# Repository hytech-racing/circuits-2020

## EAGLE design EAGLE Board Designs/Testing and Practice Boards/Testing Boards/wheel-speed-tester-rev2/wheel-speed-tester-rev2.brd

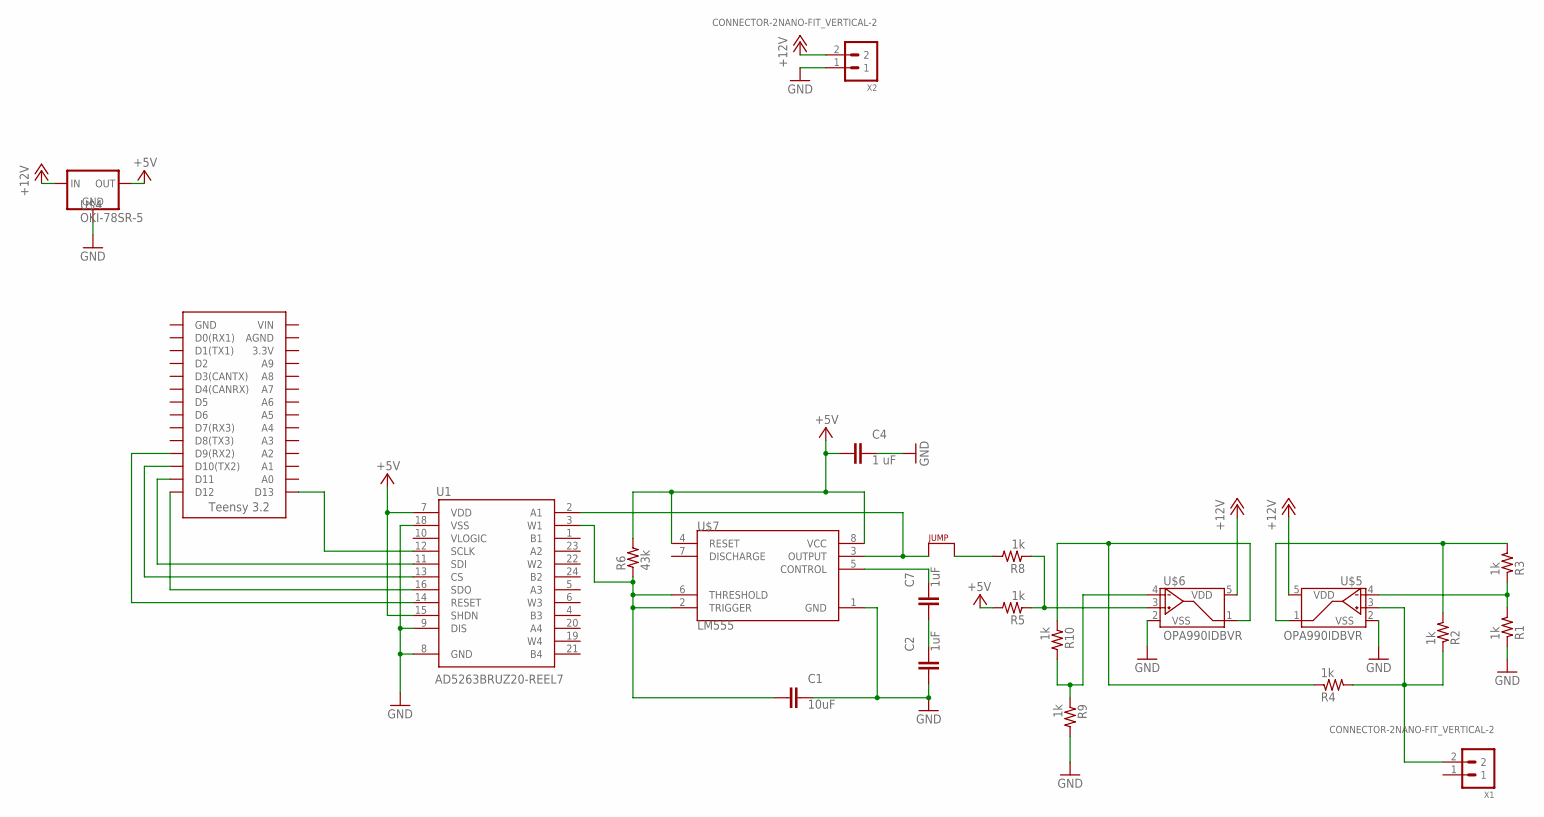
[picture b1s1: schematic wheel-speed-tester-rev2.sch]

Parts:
C1: 10uF; 0603-CAP
C2, C7: 1uF; 0603-CAP
C4: 1 uF; 0603-CAP
J2: JUMPER.1; 1X02
R1, R2, R3, R4, R5, R8, R9, R10: 1k; 0603-RES
R6: 43k; 0603-RES
U1: AD5263BRUZ20-REEL7; TSSOP-24
U$2: TEENSY_3.2_SIMPLE
U$4: OKI-78SR-5; OKI-78SR
U$5, U$6: OPA990IDBVR; SOT-23-5
U$7: LM555; SOIC-08
X1, X2: CONNECTOR-2NANO-FIT_VERTICAL-2; 1053091202

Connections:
+5V: C4.2, R5.2, R6.2, U1.7 (VDD), U1.15 (SHDN), U$4.3 (OUT), U$7.4 (RESET), U$7.8 (VCC)
+12V: U$4.1 (IN), U$5.5 (VDD), U$6.5 (VDD), X2.2
ALTERNATINGVOLTAGE: R4.1, R10.1, U$6.1 (VOUT)
CS: U1.13 (CS), U$2.D10(TX2)
GND: C1.1, C2.2, C4.1, R1.1, R9.2, U1.8 (GND), U1.9 (DIS), U1.18 (VSS), U$4.2 (GND), U$5.2 (VSS), U$6.2 (VSS), U$7.1 (GND), X2.1
unnamed: R2.2, R3.2, U$5.1 (VOUT)
unnamed: R1.2, R3.1, U$5.4 (VIN-)
unnamed: C7.1, U$7.5 (CONTROL)
unnamed: J2.2, R8.2
unnamed: R5.1, R8.1, U$6.3 (VIN+)
unnamed: C2.1, C7.2
unnamed: J2.1, U1.2 (A1), U$7.3 (OUTPUT)
unnamed: R9.1, R10.2, U$6.4 (VIN-)
unnamed: U1.11 (SDI), U$2.D11
unnamed: U1.16 (SDO), U$2.D12
unnamed: C1.2, R6.1, U1.3 (W1), U$7.2 (TRIGGER), U$7.6 (THRESHOLD)
RESET: U1.14 (RESET), U$2.D9(RX2)
SCLK: U1.12 (SCLK), U$2.D13
WSTESTER_OUT: R2.1, R4.2, U$5.3 (VIN+), X1.2

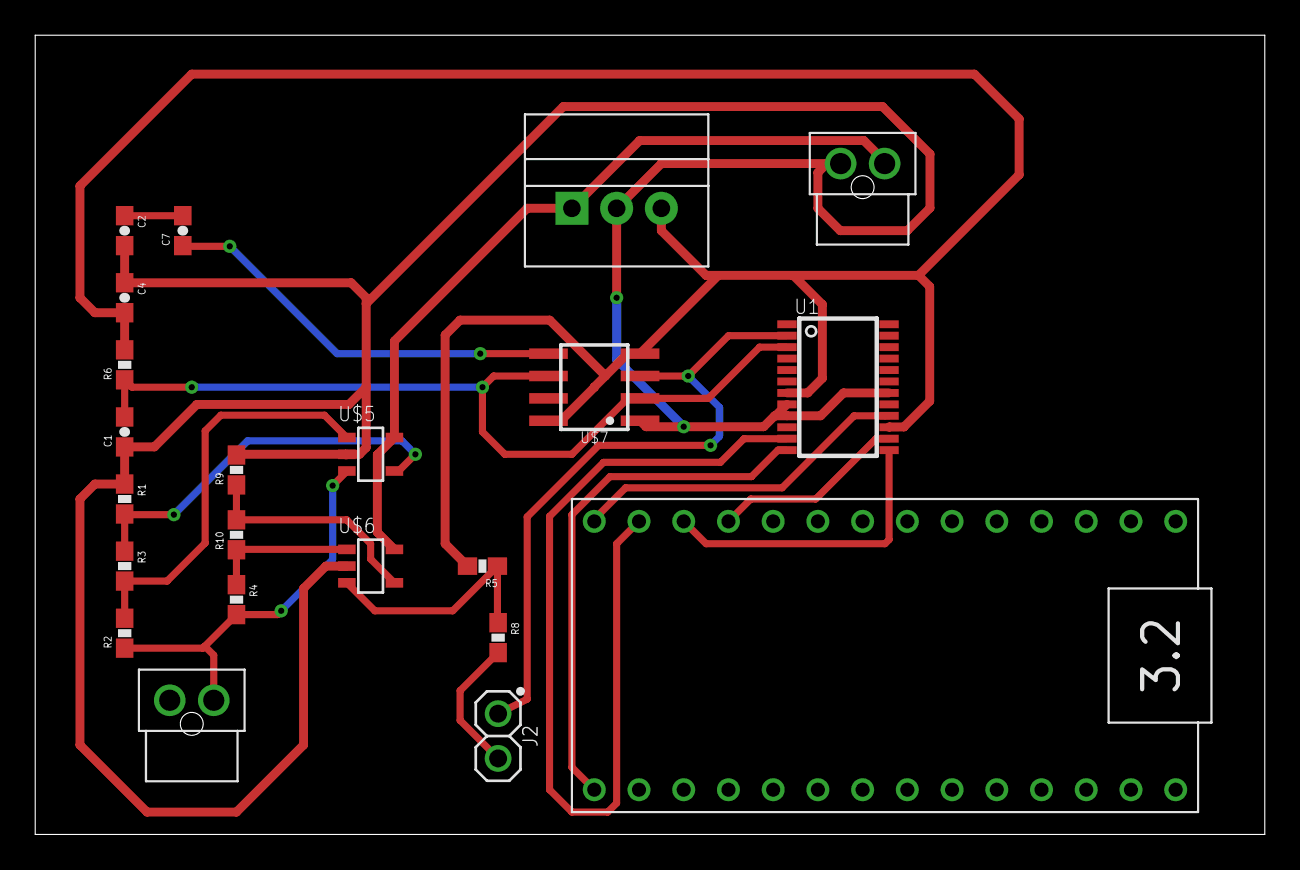
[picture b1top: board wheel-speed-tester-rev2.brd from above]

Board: 2 copper layers, 69.8 x 45.4 mm, 22 parts (0 on the bottom side), 19 nets.

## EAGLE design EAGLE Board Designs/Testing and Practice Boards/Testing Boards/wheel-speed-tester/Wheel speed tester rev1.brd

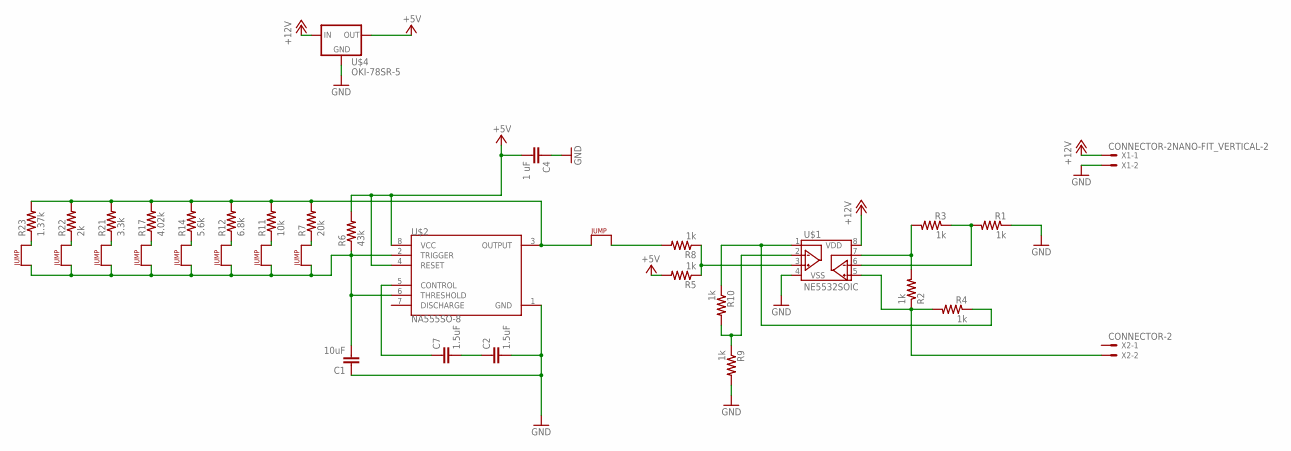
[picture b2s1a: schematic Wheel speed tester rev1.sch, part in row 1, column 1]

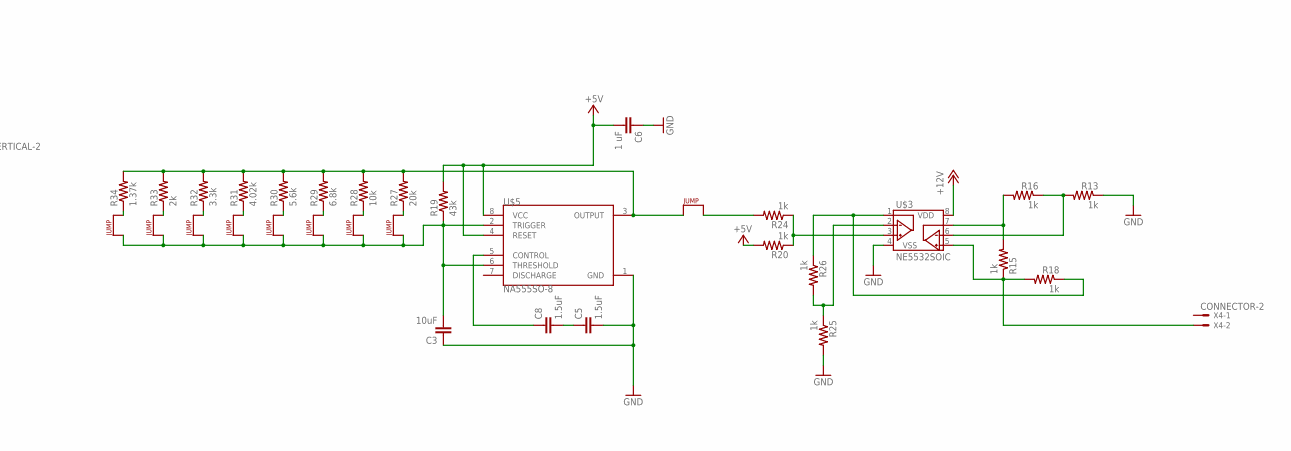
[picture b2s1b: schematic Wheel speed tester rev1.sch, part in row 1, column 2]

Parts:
C1, C3: 10uF; 0603-CAP
C2, C5, C7, C8: 1.5uF; 0603-CAP
C4, C6: 1 uF; 0603-CAP
J1, J2, J3, J4, J5, J6, J7, J8, J9, J10, J11, J12, J13, J14, J15, J16, J17, J18: JUMPER.1; 1X02
R1, R2, R3, R4, R5, R8, R9, R10, R13, R15, R16, R18, R20, R24, R25, R26: 1k; 0603-RES
R6, R19: 43k; 0603-RES
R7, R27: 20k; 0603-RES
R11, R28: 10k; 0603-RES
R12, R29: 6.8k; 0603-RES
R14, R30: 5.6k; 0603-RES
R17, R31: 4.02k; 0603-RES
R21, R32: 3.3k; 0603-RES
R22, R33: 2k; 0603-RES
R23, R34: 1.37k; 0603-RES
U$1, U$3: NE5532SOIC; SOIC-08
U$2, U$5: NA555SO-8; SOIC-08
U$4: OKI-78SR-5; OKI-78SR
X1: CONNECTOR-2NANO-FIT_VERTICAL-2; NANO-FIT_VERTICAL-2
X2, X4: CONNECTOR-2; MINIFIT_5566-2

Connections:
+5V: C4.2, C6.2, R5.2, R6.2, R19.2, R20.2, U$2.4 (RESET), U$2.8 (VCC), U$4.3 (OUT), U$5.4 (RESET), U$5.8 (VCC)
+12V: U$1.8 (VDD), U$3.8 (VDD), U$4.1 (IN), X1.P$1
ALTERNATINGVOLTAGE: R4.1, R10.1, U$1.1 (VOUTA)
ALTERNATINGVOLTAGE1: R18.1, R26.1, U$3.1 (VOUTA)
GND: C1.1, C2.2, C3.1, C4.1, C5.2, C6.1, R1.1, R9.2, R13.1, R25.2, U$1.4 (VSS), U$2.1 (GND), U$3.4 (VSS), U$4.2 (GND), U$5.1 (GND), X1.P$2
unnamed: R2.2, R3.2, U$1.7 (VOUTB)
unnamed: R1.2, R3.1, U$1.6 (VINB-)
unnamed: C7.1, U$2.5 (CONTROL)
unnamed: J2.2, R8.2
unnamed: C1.2, J1.1, J3.1, J4.1, J5.1, J6.1, J7.1, J8.1, J9.1, R6.1, U$2.2 (TRIGGER), U$2.6 (THRESHOLD)
unnamed: R5.1, R8.1, U$1.3 (VINA+)
unnamed: J9.2, R7.1
unnamed: J2.1, R7.2, R11.2, R12.2, R14.2, R17.2, R21.2, R22.2, R23.2, U$2.3 (OUTPUT)
unnamed: R9.1, R10.2, U$1.2 (VINA-)
unnamed: J8.2, R11.1
unnamed: J7.2, R12.1
unnamed: J6.2, R14.1
unnamed: J5.2, R17.1
unnamed: J4.2, R21.1
unnamed: J3.2, R22.1
unnamed: J1.2, R23.1
unnamed: R13.2, R16.1, U$3.6 (VINB-)
unnamed: J10.1, R27.2, R28.2, R29.2, R30.2, R31.2, R32.2, R33.2, R34.2, U$5.3 (OUTPUT)
unnamed: R20.1, R24.1, U$3.3 (VINA+)
unnamed: R15.2, R16.2, U$3.7 (VOUTB)
unnamed: R25.1, R26.2, U$3.2 (VINA-)
unnamed: C3.2, J11.1, J12.1, J13.1, J14.1, J15.1, J16.1, J17.1, J18.1, R19.1, U$5.2 (TRIGGER), U$5.6 (THRESHOLD)
unnamed: C8.1, U$5.5 (CONTROL)
unnamed: J10.2, R24.2
unnamed: J18.2, R27.1
unnamed: J17.2, R28.1
unnamed: J16.2, R29.1
unnamed: J15.2, R30.1
unnamed: J14.2, R31.1
unnamed: J13.2, R32.1
unnamed: J12.2, R33.1
unnamed: J11.2, R34.1
unnamed: C2.1, C7.2
unnamed: C5.1, C8.2
SENSOROUT: R2.1, R4.2, U$1.5 (VINB+), X2.2
SENSOROUT1: R15.1, R18.2, U$3.5 (VINB+), X4.2

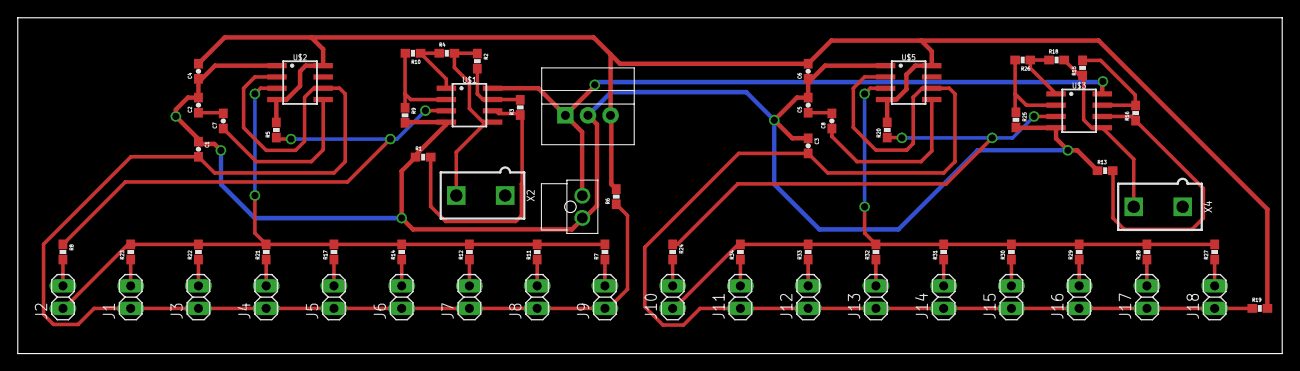
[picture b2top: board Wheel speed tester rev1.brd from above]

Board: 2 copper layers, 142.2 x 37.8 mm, 68 parts (0 on the bottom side), 41 nets.

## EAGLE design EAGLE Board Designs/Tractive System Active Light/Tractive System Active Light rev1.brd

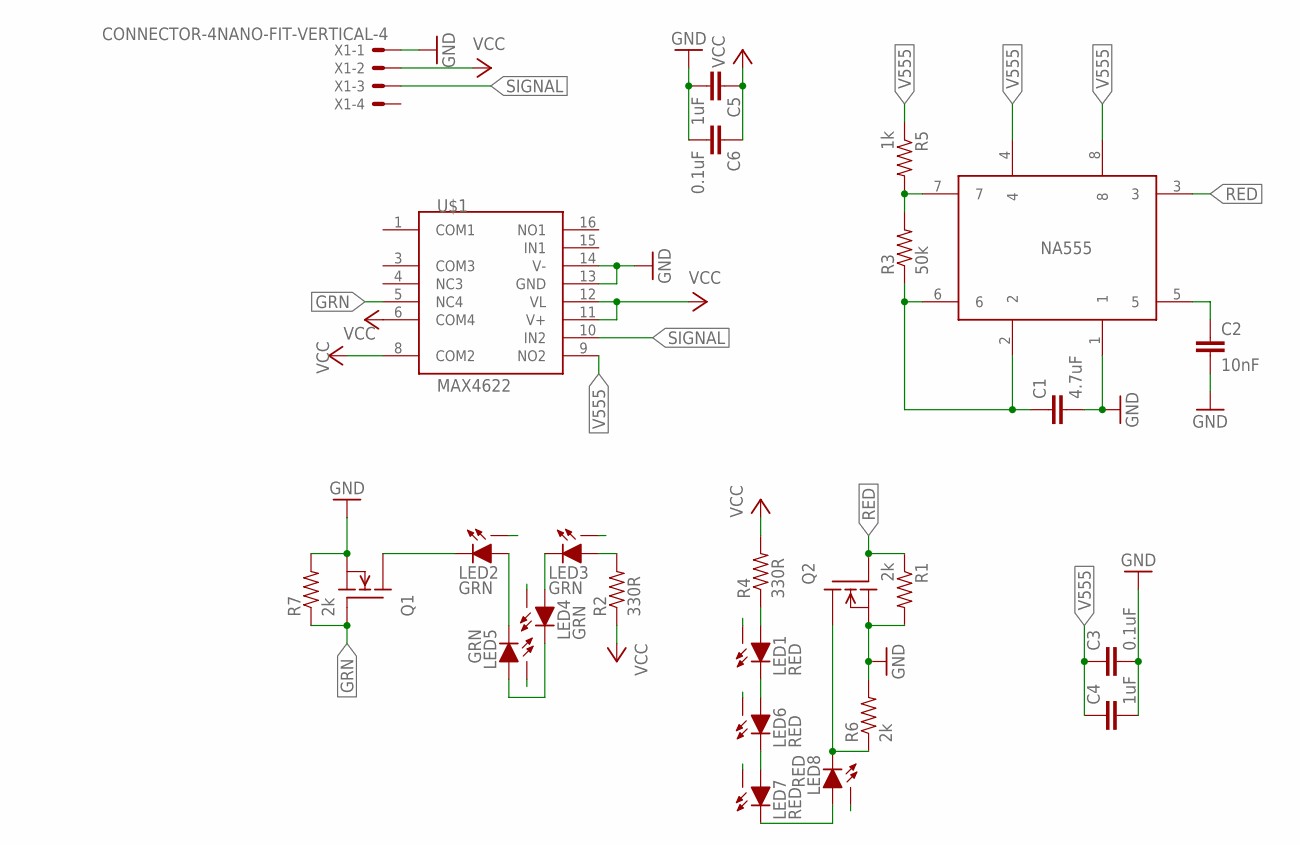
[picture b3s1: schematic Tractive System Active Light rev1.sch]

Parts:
C1: 4.7uF; 0603-CAP; TOLERANCE 5%; VOLTAGE 25V
C2: 10nF; 0603-CAP; TOLERANCE 5%; VOLTAGE 25V
C3, C6: 0.1uF; 0603-CAP; TOLERANCE 5%; VOLTAGE 25V
C4, C5: 1uF; 0603-CAP; TOLERANCE 5%; VOLTAGE 25V
LED1, LED6, LED7, LED8: RED; XP-E2
LED2, LED3, LED4, LED5: GRN; XP-E2
NA555: NA555SO-8; SOIC-08
Q1, Q2: DMG3406LSOT; SOT23
R1, R6, R7: 2k; 0603-RES; TOLERANCE 1%
R2, R4: 330R; 0603-RES; TOLERANCE 1%
R3: 50k; 0603-RES; TOLERANCE 1%
R5: 1k; 0603-RES; TOLERANCE 1%
U$1: MAX4622; SO16
X1: CONNECTOR-4NANO-FIT-VERTICAL-4; NANO-FIT_VERTICAL-4

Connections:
GND: C1.2, C2.2, C3.2, C4.2, C5.2, C6.2, NA555.1, Q1.2 (S), Q2.2 (S), R1.2, R6.2, R7.2, U$1.13 (GND), U$1.14 (V-), X1.P$1
GRN: Q1.1 (G), R7.1, U$1.5 (NC4)
LED1_THERM: LED1.X
LED2_THERM: LED2.X
LED3_THERM: LED3.X
LED4_THERM: LED4.X
LED5_THERM: LED5.X
LED6_THERM: LED6.X
LED7_THERM: LED7.X
LED8_THERM: LED8.X
unnamed: LED4.C, LED5.A
unnamed: LED2.C, Q1.3 (D)
unnamed: LED3.C, LED4.A
unnamed: LED3.A, R2.2
unnamed: C1.1, NA555.2, NA555.6, R3.1
unnamed: NA555.7, R3.2, R5.2
unnamed: LED8.C, Q2.3 (D), R6.1
unnamed: LED1.A, R4.1
unnamed: C2.1, NA555.5
unnamed: LED2.A, LED5.C
unnamed: LED1.C, LED6.A
unnamed: LED6.C, LED7.A
unnamed: LED7.C, LED8.A
RED: NA555.3, Q2.1 (G), R1.1
SIGNAL: U$1.10 (IN2), X1.P$3
V555: C3.1, C4.1, NA555.4, NA555.8, R5.1, U$1.9 (NO2)
VCC: C5.1, C6.1, R2.1, R4.2, U$1.6 (COM4), U$1.8 (COM2), U$1.11 (V+), U$1.12 (VL), X1.P$2

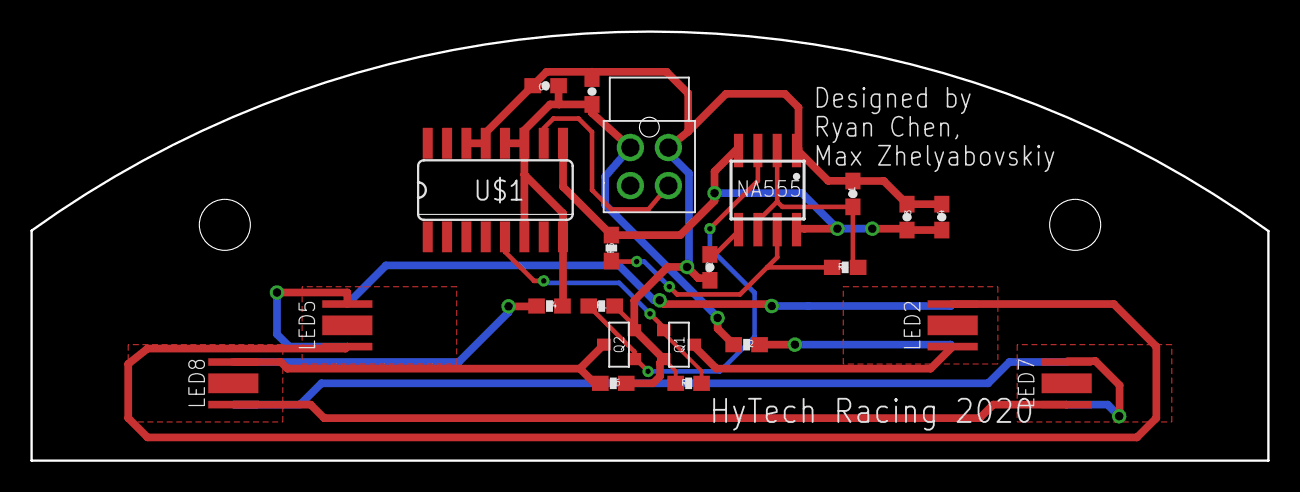
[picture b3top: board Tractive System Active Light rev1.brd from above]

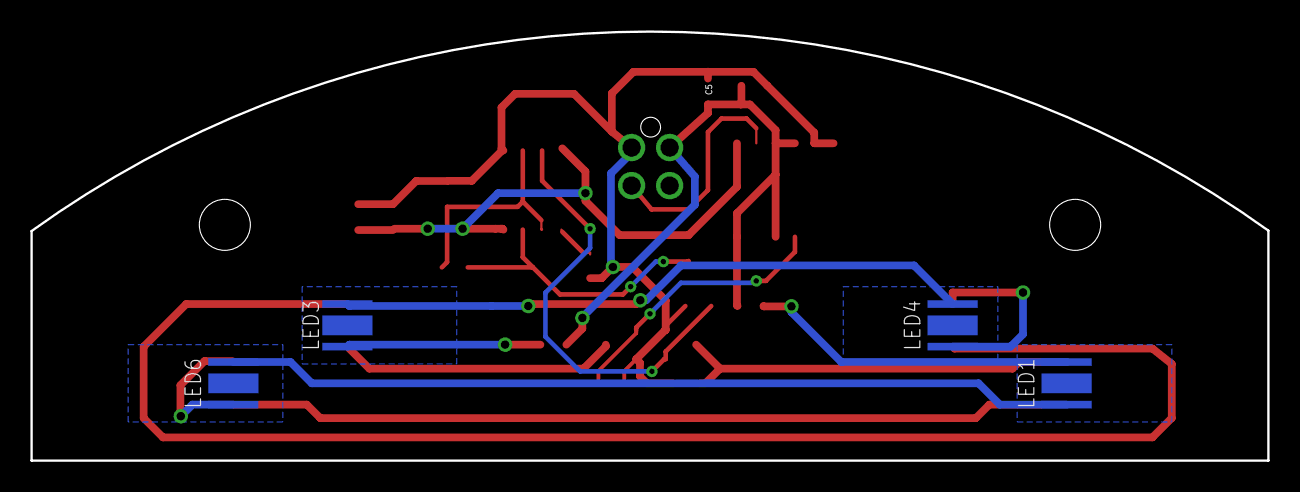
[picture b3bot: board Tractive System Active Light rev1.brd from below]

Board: 2 copper layers, 81.3 x 28.2 mm, 26 parts (4 on the bottom side), 19 nets.

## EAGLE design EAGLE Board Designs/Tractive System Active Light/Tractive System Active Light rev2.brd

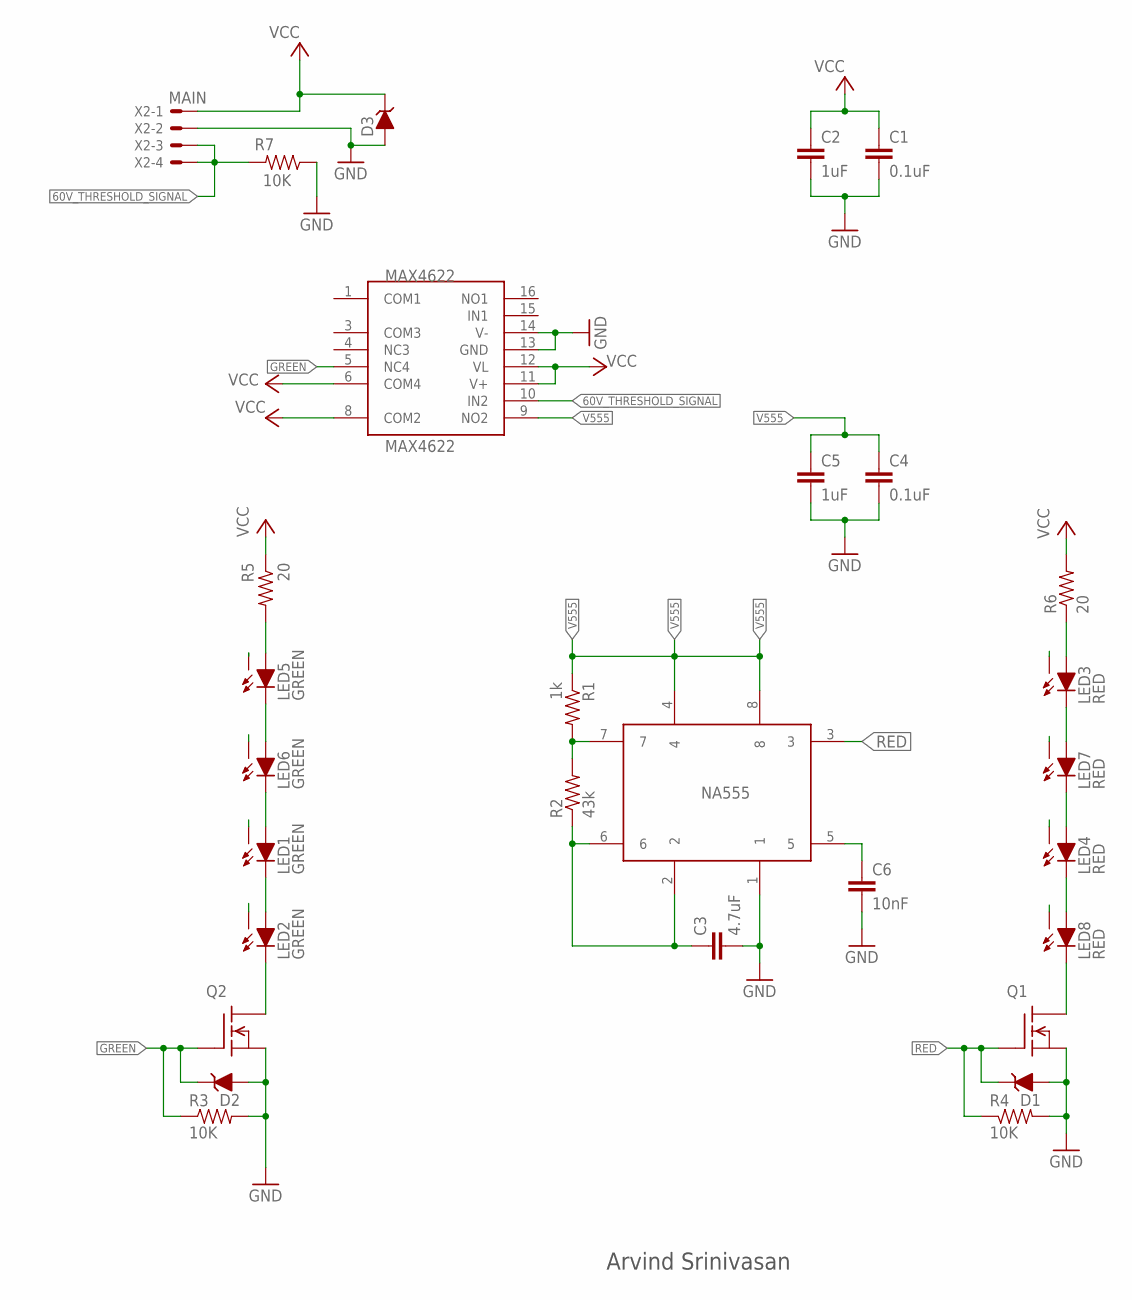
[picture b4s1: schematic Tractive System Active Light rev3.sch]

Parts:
C1, C4: 0.1uF; 0603-CAP; TOLERANCE 5%; VOLTAGE 25V
C2, C5: 1uF; 0603-CAP; TOLERANCE 5%; VOLTAGE 25V
C3: 4.7uF; 0603-CAP; TOLERANCE 5%; VOLTAGE 25V
C6: 10nF; 0603-CAP; TOLERANCE 5%; VOLTAGE 25V
D1, D2: MMBZ5246BLT1G; SOT23
D3: D15V0S1U2LP1608; 0603_D
LED1, LED2, LED5, LED6: GREEN; XP-E2
LED3, LED4, LED7, LED8: RED; XP-E2
MAX4622: MAX4622; SO16
NA555: NA555SO-8; SOIC-08
Q1, Q2: DMG3406LSOT; SOT23
R1: 1k; 0603-RES; TOLERANCE 1%
R2: 43k; 0603-RES; TOLERANCE 1%
R3, R4, R7: 10K; 0603-RES; TOLERANCE 1%
R5, R6: 20; 0603-RES; TOLERANCE 1%
X2: MAIN; NANO-FIT_RIGHT_ANGLE-4-SURFACE

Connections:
60V_THRESHOLD_SIGNAL: MAX4622.10 (IN2), R7.2, X2.3, X2.4
GND: C1.2, C2.2, C3.2, C4.2, C5.2, C6.2, D1.1 (A), D2.1 (A), D3.A, MAX4622.13 (GND), MAX4622.14 (V-), NA555.1, Q1.2 (S), Q2.2 (S), R3.2, R4.2, R7.1, X2.2
GREEN: D2.3 (C), MAX4622.5 (NC4), Q2.1 (G), R3.1
unnamed: LED1.A, LED6.C
unnamed: LED2.C, Q2.3 (D)
unnamed: LED5.C, LED6.A
unnamed: LED5.A, R5.2
unnamed: C3.1, NA555.2, NA555.6, R2.1
unnamed: NA555.7, R1.2, R2.2
unnamed: LED8.C, Q1.3 (D)
unnamed: LED3.A, R6.1
unnamed: C6.1, NA555.5
unnamed: LED1.C, LED2.A
unnamed: LED3.C, LED7.A
unnamed: LED4.A, LED7.C
unnamed: LED4.C, LED8.A
RED: D1.3 (C), NA555.3, Q1.1 (G), R4.1
THERM: LED1.X, LED2.X, LED3.X, LED4.X, LED5.X, LED6.X, LED7.X, LED8.X
V555: C4.1, C5.1, MAX4622.9 (NO2), NA555.4, NA555.8, R1.1
VCC: C1.1, C2.1, D3.C, MAX4622.6 (COM4), MAX4622.8 (COM2), MAX4622.11 (V+), MAX4622.12 (VL), R5.1, R6.2, X2.1

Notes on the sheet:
Arvind Srinivasan

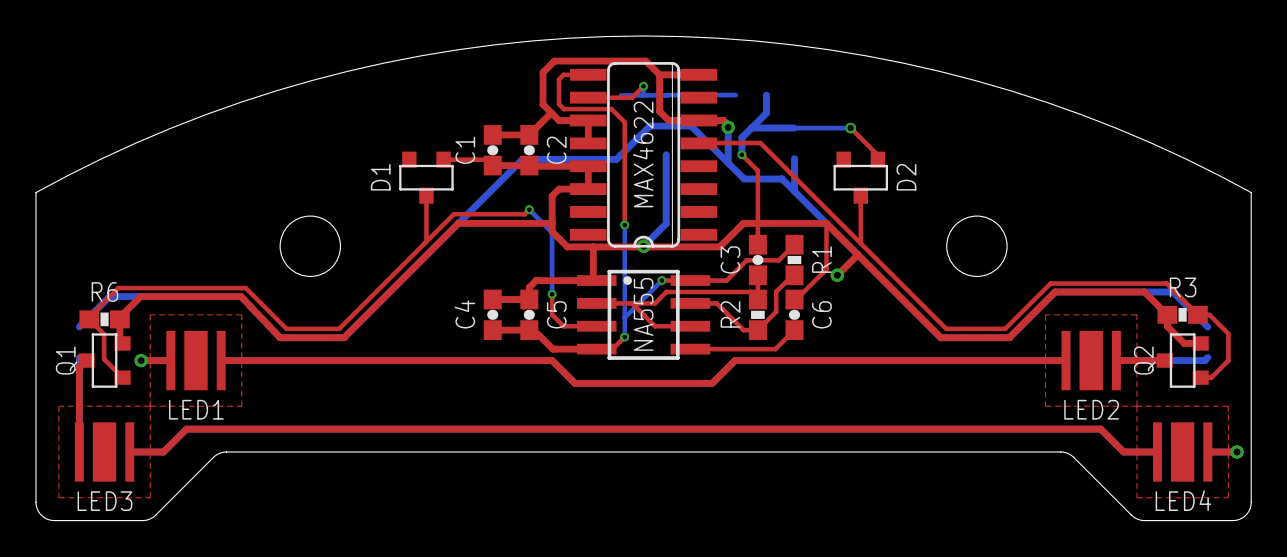
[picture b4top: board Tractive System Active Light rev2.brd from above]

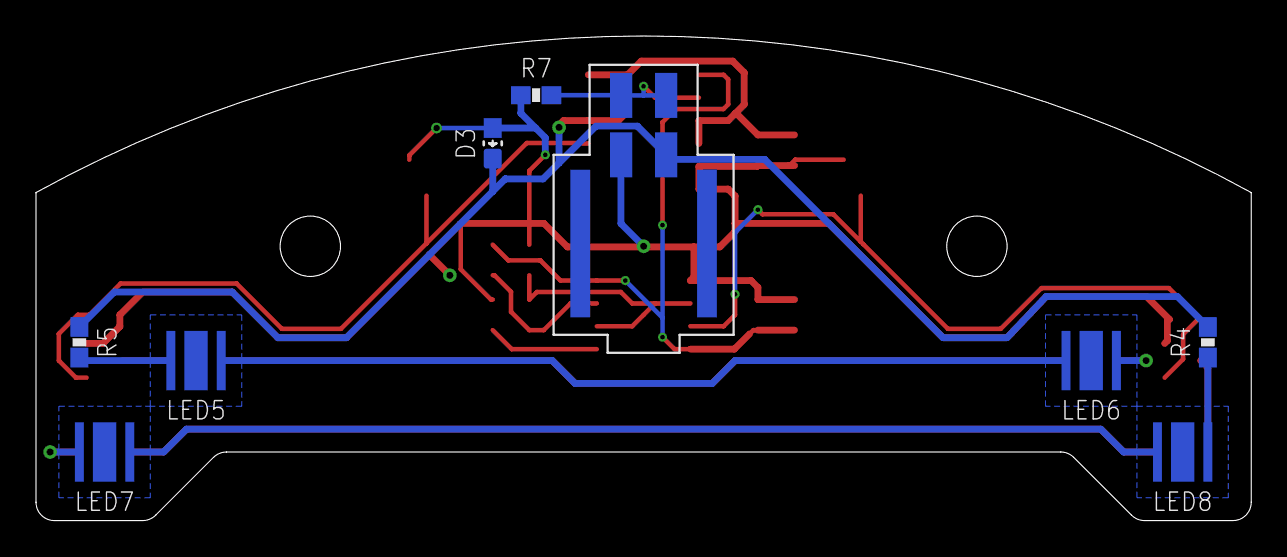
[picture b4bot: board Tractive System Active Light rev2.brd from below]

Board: 2 copper layers, 67.5 x 26.9 mm, 31 parts (9 on the bottom side), 20 nets.

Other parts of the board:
$$U$1: M3_MOUNTING
U$2: M3_MOUNTING
